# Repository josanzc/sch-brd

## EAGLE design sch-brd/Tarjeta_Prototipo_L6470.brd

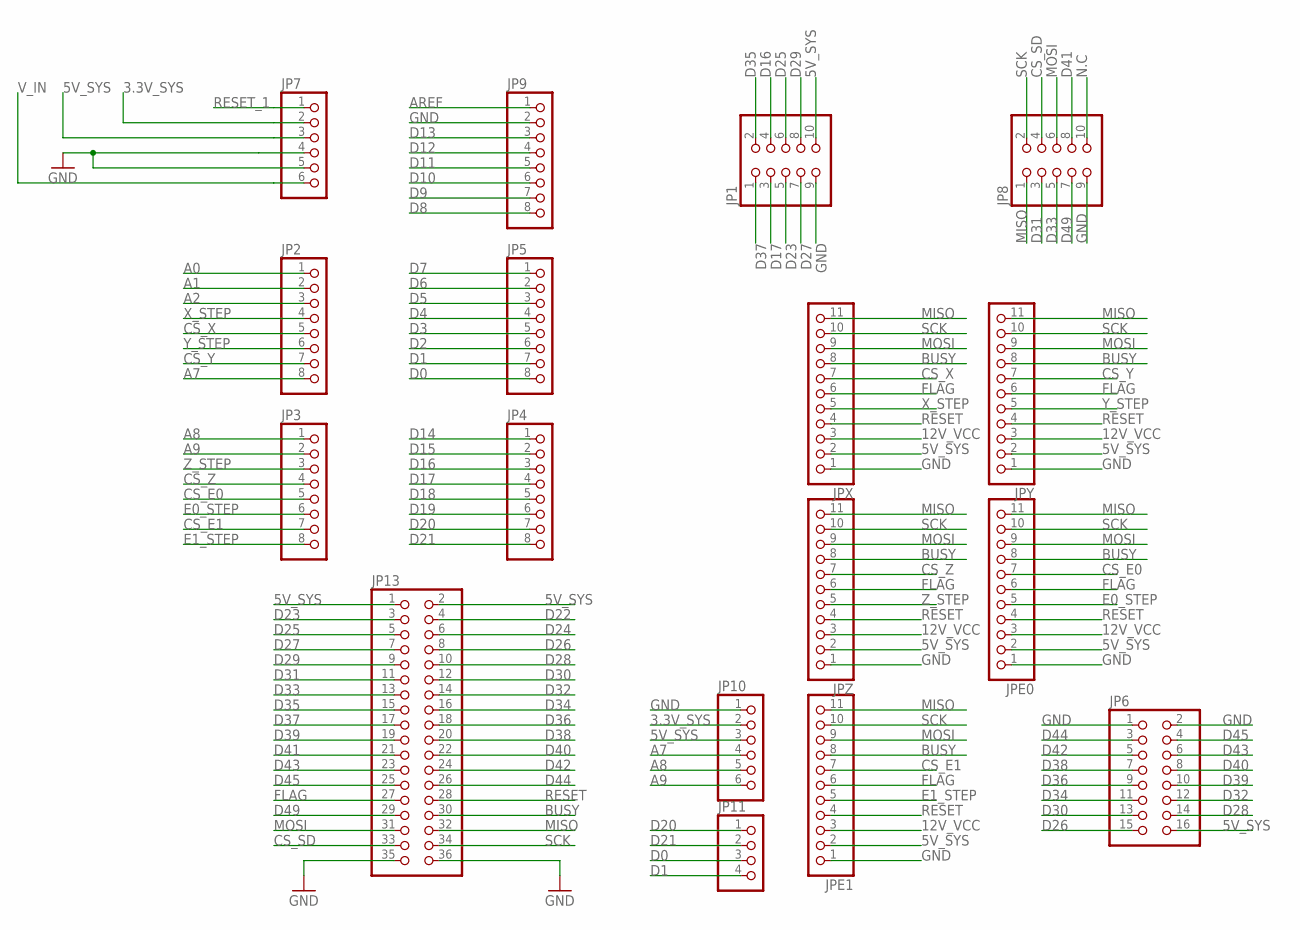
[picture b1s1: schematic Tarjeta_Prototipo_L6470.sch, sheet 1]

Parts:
JP1, JP8: PINHD-2X5; 2X05
JP2, JP3, JP4, JP5, JP9: PINHD-1X8; 1X08
JP6: PINHD-2X8; 2X08
JP7, JP10: PINHD-1X6; 1X06
JP11: PINHD-1X4; 1X04
JP13: PINHD-2X18; 2X18
JPE0, JPE1: PINHD-1X11; 1X11
JPX: PINHD-1X11; 1X11
JPY: PINHD-1X11; 1X11
JPZ: PINHD-1X11; 1X11

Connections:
3.3V_SYS: JP7.2, JP10.2
5V_SYS: JP1.10, JP6.16, JP7.3, JP10.3, JP13.1, JP13.2, JPE0.2, JPE1.2, JPX.2, JPY.2, JPZ.2; also elsewhere on the board
12V_VCC: JPE0.3, JPE1.3, JPX.3, JPY.3, JPZ.3; also elsewhere on the board
A0: JP2.1; also elsewhere on the board
A1: JP2.2; also elsewhere on the board
A2: JP2.3; also elsewhere on the board
A7: JP2.8, JP10.4
A8: JP3.1, JP10.5
A9: JP3.2, JP10.6
AREF: JP9.1
BUSY: JP13.30, JPE0.8, JPE1.8, JPX.8, JPY.8, JPZ.8
CS_E0: JP3.5, JPE0.7
CS_E1: JP3.7, JPE1.7
CS_SD: JP8.4, JP13.33
CS_X: JP2.5, JPX.7
CS_Y: JP2.7, JPY.7
CS_Z: JP3.4, JPZ.7
D0: JP5.8, JP11.3
D1: JP5.7, JP11.4
D2: JP5.6; also elsewhere on the board
D3: JP5.5; also elsewhere on the board
D4: JP5.4; also elsewhere on the board
D5: JP5.3; also elsewhere on the board
D6: JP5.2; also elsewhere on the board
D7: JP5.1; also elsewhere on the board
D8: JP9.8; also elsewhere on the board
D9: JP9.7; also elsewhere on the board
D10: JP9.6; also elsewhere on the board
D11: JP9.5; also elsewhere on the board
D12: JP9.4; also elsewhere on the board
D13: JP9.3; also elsewhere on the board
D14: JP4.1; also elsewhere on the board
D15: JP4.2; also elsewhere on the board
D16: JP1.4, JP4.3
D17: JP1.3, JP4.4
D18: JP4.5; also elsewhere on the board
D19: JP4.6; also elsewhere on the board
D20: JP4.7, JP11.1
D21: JP4.8, JP11.2
D22: JP13.4; also elsewhere on the board
D23: JP1.5, JP13.3
D24: JP13.6; also elsewhere on the board
D25: JP1.6, JP13.5
D26: JP6.15, JP13.8
D27: JP1.7, JP13.7
D28: JP6.14, JP13.10
D29: JP1.8, JP13.9
D30: JP6.13, JP13.12
D31: JP8.3, JP13.11
D32: JP6.12, JP13.14
D33: JP8.5, JP13.13
D34: JP6.11, JP13.16
D35: JP1.2, JP13.15
D36: JP6.9, JP13.18
D37: JP1.1, JP13.17
D38: JP6.7, JP13.20
D39: JP6.10, JP13.19
D40: JP6.8, JP13.22
D41: JP8.8, JP13.21
D42: JP6.5, JP13.24
D43: JP6.6, JP13.23
D44: JP6.3, JP13.26
D45: JP6.4, JP13.25
D49: JP8.7, JP13.29
E0_STEP: JP3.6, JPE0.5
E1_STEP: JP3.8, JPE1.5
FLAG: JP13.27, JPE0.6, JPE1.6, JPX.6, JPY.6, JPZ.6
GND: JP1.9, JP6.1, JP6.2, JP7.4, JP7.5, JP8.9, JP9.2, JP10.1, JP13.35, JP13.36, JPE0.1, JPE1.1, JPX.1, JPY.1, JPZ.1; also elsewhere on the board
MISO: JP8.1, JP13.32, JPE0.11, JPE1.11, JPX.11, JPY.11, JPZ.11
MOSI: JP8.6, JP13.31, JPE0.9, JPE1.9, JPX.9, JPY.9, JPZ.9
N.C: JP8.10
RESET: JP13.28, JPE0.4, JPE1.4, JPX.4, JPY.4, JPZ.4
RESET_1: JP7.1; also elsewhere on the board
SCK: JP8.2, JP13.34, JPE0.10, JPE1.10, JPX.10, JPY.10, JPZ.10
V_IN: JP7.6; also elsewhere on the board
X_STEP: JP2.4, JPX.5
Y_STEP: JP2.6, JPY.5
Z_STEP: JP3.3, JPZ.5

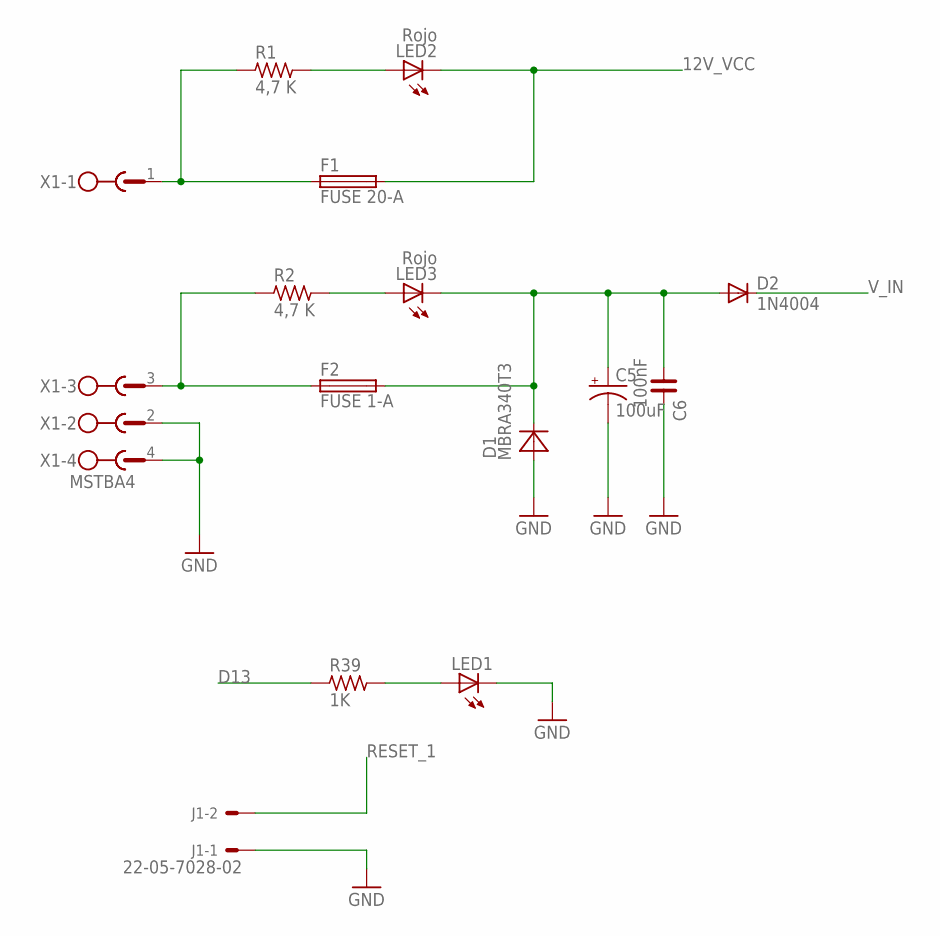
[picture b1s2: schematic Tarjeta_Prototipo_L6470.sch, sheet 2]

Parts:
C5: 100uF; 153CLV-0605
C6: 100nF; C1206
D1: MBRA340T3; SMA
D2: 1N4004; DO41-10
F1: FUSE 20-A; 3557
F2: FUSE 1-A; 3557
J1: 22-05-7028-02; 7395-02
LED1: LEDSMT1206; 1206
LED2, LED3: Rojo; 1206
R1, R2: 4,7 K; R1206
R39: 1K; R1206
X1: MSTBA4

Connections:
12V_IN1: F1.P$1 (1), F1.P$2 (1), R1.1, X1.1
12V_IN2: F2.P$1 (1), F2.P$2 (1), R2.1, X1.3
12V_VCC: F1.P$3 (2), F1.P$4 (2), LED2.C; also elsewhere on the board
D13: R39.1; also elsewhere on the board
GND: C5.-, C6.2, D1.A, J1.1, LED1.C, X1.2, X1.4; also elsewhere on the board
unnamed: LED1.A, R39.2
unnamed: LED2.A, R1.2
unnamed: LED3.A, R2.2
unnamed: C5.+, C6.1, D1.C, D2.A, F2.P$3 (2), F2.P$4 (2), LED3.C
RESET_1: J1.2; also elsewhere on the board
V_IN: D2.C; also elsewhere on the board

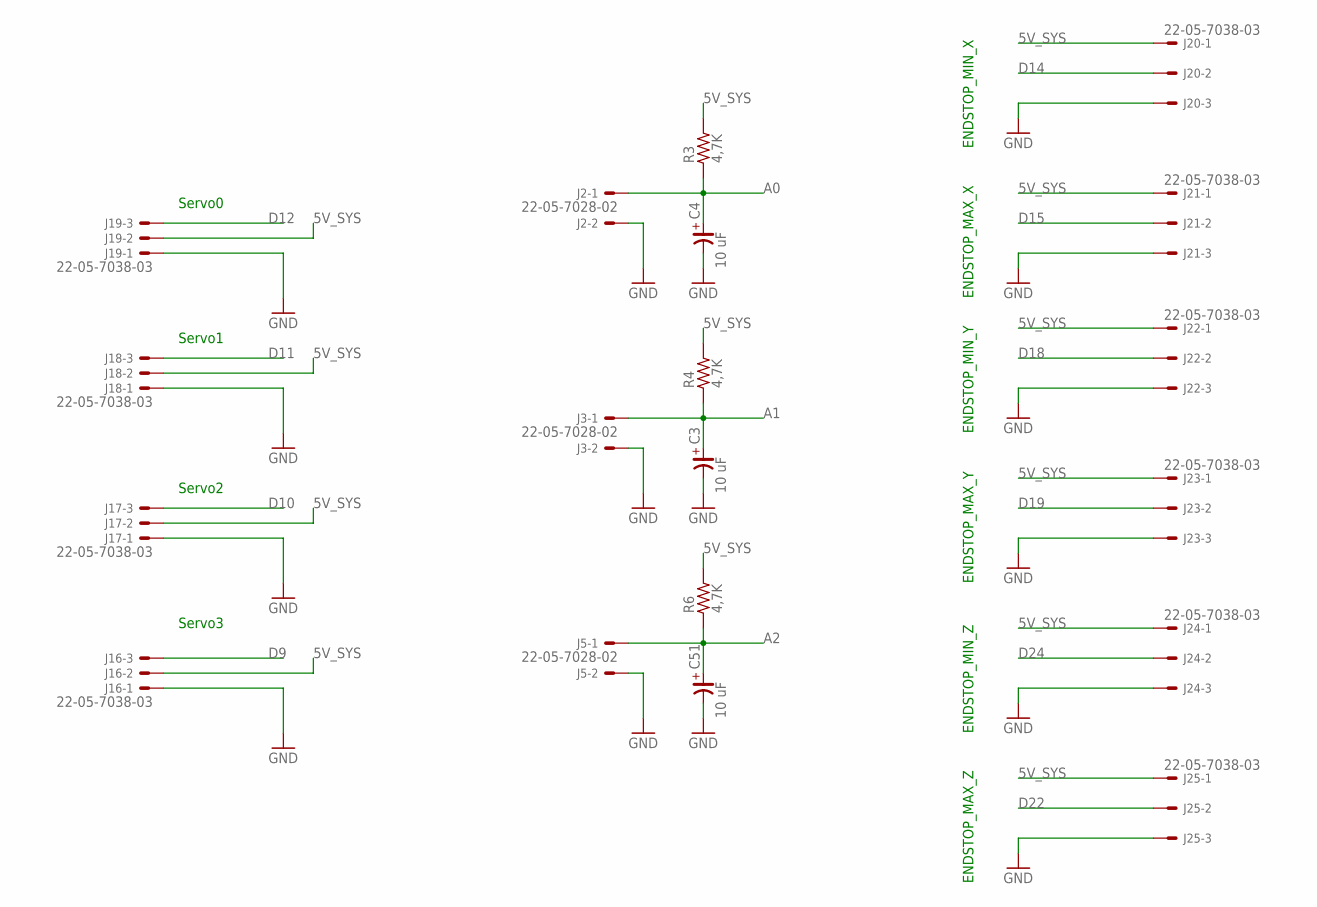
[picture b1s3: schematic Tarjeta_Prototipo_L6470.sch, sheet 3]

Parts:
C3, C4, C51: 10 uF; CSV-B
J2, J3, J5: 22-05-7028-02; 7395-02
J16, J17, J18, J19, J20, J21, J22, J23, J24, J25: 22-05-7038-03; 7395-03
R3, R4, R6: 4,7K; R1206

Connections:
5V_SYS: J16.2, J17.2, J18.2, J19.2, J20.1, J21.1, J22.1, J23.1, J24.1, J25.1, R3.2, R4.2, R6.2; also elsewhere on the board
A0: C4.+, J2.1, R3.1; also elsewhere on the board
A1: C3.+, J3.1, R4.1; also elsewhere on the board
A2: C51.+, J5.1, R6.1; also elsewhere on the board
D9: J16.3; also elsewhere on the board
D10: J17.3; also elsewhere on the board
D11: J18.3; also elsewhere on the board
D12: J19.3; also elsewhere on the board
D14: J20.2; also elsewhere on the board
D15: J21.2; also elsewhere on the board
D18: J22.2; also elsewhere on the board
D19: J23.2; also elsewhere on the board
D22: J25.2; also elsewhere on the board
D24: J24.2; also elsewhere on the board
GND: C3.-, C4.-, C51.-, J2.2, J3.2, J5.2, J16.1, J17.1, J18.1, J19.1, J20.3, J21.3, J22.3, J23.3, J24.3, J25.3; also elsewhere on the board

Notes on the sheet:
Servo3
Servo2
Servo1
Servo0
ENDSTOP_MIN_X
ENDSTOP_MAX_X
ENDSTOP_MIN_Y
ENDSTOP_MAX_Y
ENDSTOP_MAX_Z
ENDSTOP_MIN_Z

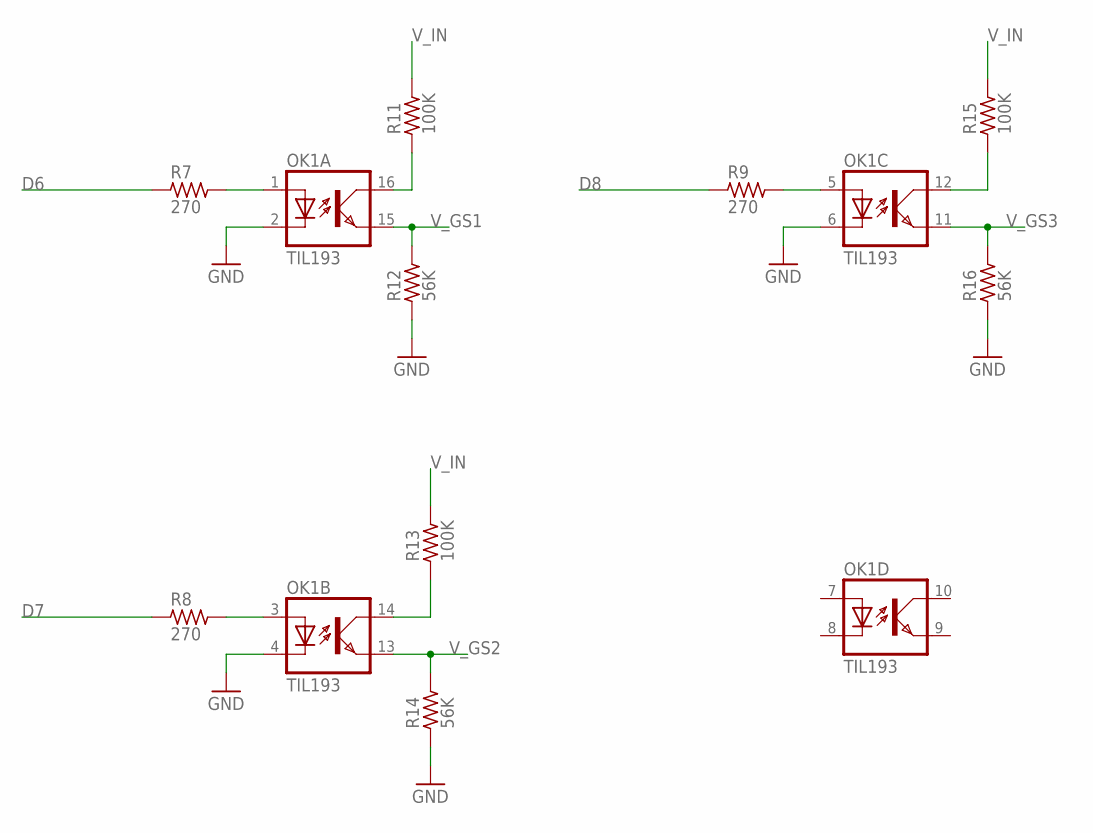
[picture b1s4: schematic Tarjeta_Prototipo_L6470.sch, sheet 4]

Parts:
OK1: TIL193; DIL16
R7, R8, R9: 270; R1206
R11, R13, R15: 100K; R1206
R12, R14, R16: 56K; R1206

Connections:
D6: R7.1; also elsewhere on the board
D7: R8.1; also elsewhere on the board
D8: R9.1; also elsewhere on the board
GND: OK1.2 (C), OK1.4 (C), OK1.6 (C), R12.1, R14.1, R16.1; also elsewhere on the board
unnamed: OK1.1 (A), R7.2
unnamed: OK1.3 (A), R8.2
unnamed: OK1.5 (A), R9.2
unnamed: OK1.16 (COL), R11.1
unnamed: OK1.14 (COL), R13.1
unnamed: OK1.12 (COL), R15.1
V_GS1: OK1.15 (EMIT), R12.2; also elsewhere on the board
V_GS2: OK1.13 (EMIT), R14.2; also elsewhere on the board
V_GS3: OK1.11 (EMIT), R16.2; also elsewhere on the board
V_IN: R11.2, R13.2, R15.2; also elsewhere on the board

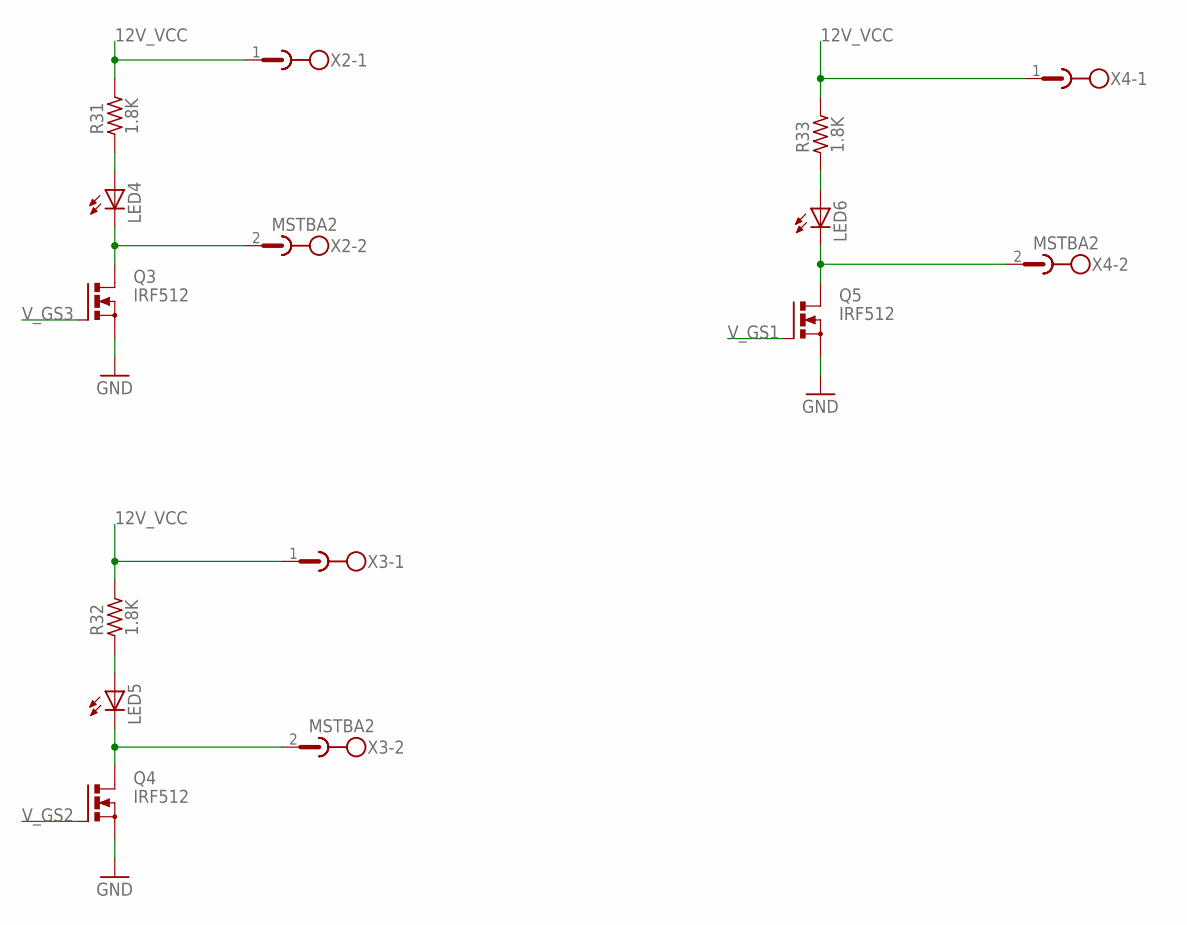
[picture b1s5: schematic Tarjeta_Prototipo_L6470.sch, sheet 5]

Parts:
LED4, LED5, LED6: LEDSMT1206; 1206
Q3, Q4, Q5: IRF512; TO220BV
R31, R32, R33: 1.8K; R1206
X2, X3, X4: MSTBA2

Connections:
12V_VCC: R31.2, R32.2, R33.2, X2.1, X3.1, X4.1; also elsewhere on the board
GND: Q3.S, Q4.S, Q5.S; also elsewhere on the board
unnamed: LED6.C, Q5.D, X4.2
unnamed: LED4.A, R31.1
unnamed: LED5.C, Q4.D, X3.2
unnamed: LED5.A, R32.1
unnamed: LED6.A, R33.1
unnamed: LED4.C, Q3.D, X2.2
V_GS1: Q5.G; also elsewhere on the board
V_GS2: Q4.G; also elsewhere on the board
V_GS3: Q3.G; also elsewhere on the board

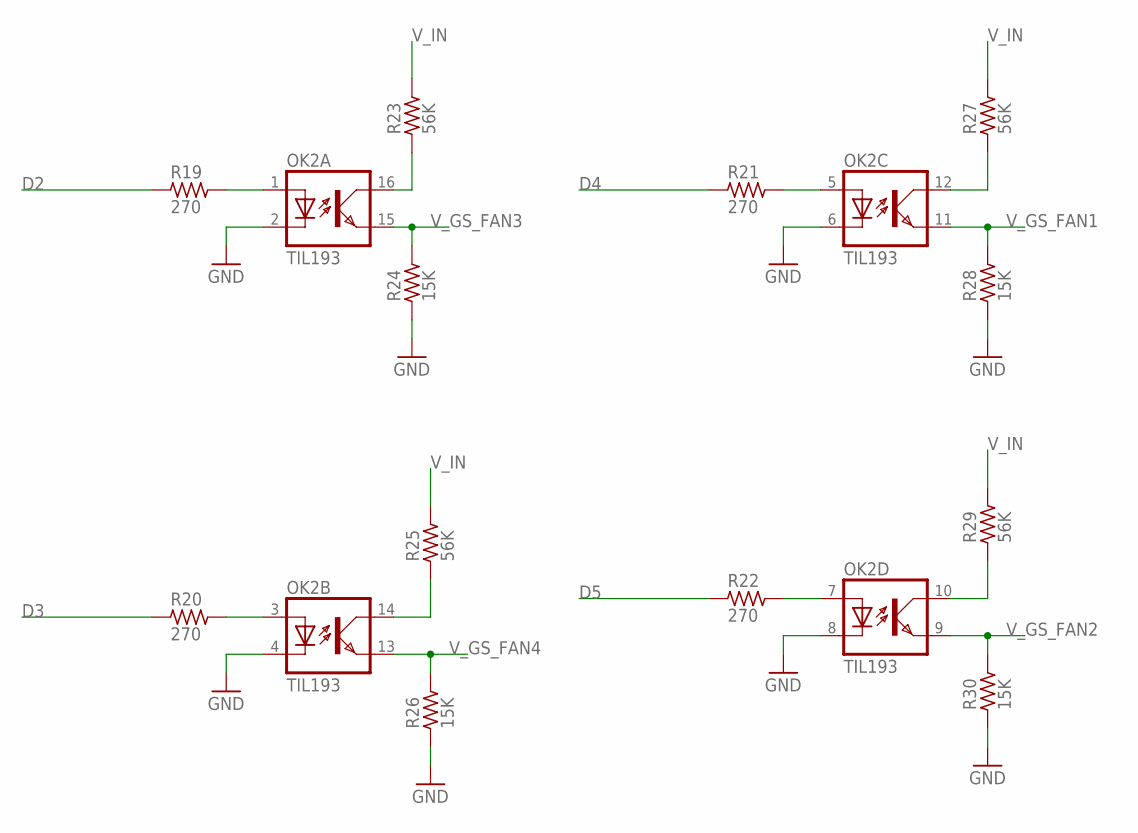
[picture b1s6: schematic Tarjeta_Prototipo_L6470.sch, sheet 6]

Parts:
OK2: TIL193; DIL16
R19, R20, R21, R22: 270; R1206
R23, R25, R27, R29: 56K; R1206
R24, R26, R28, R30: 15K; R1206

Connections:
D2: R19.1; also elsewhere on the board
D3: R20.1; also elsewhere on the board
D4: R21.1; also elsewhere on the board
D5: R22.1; also elsewhere on the board
GND: OK2.2 (C), OK2.4 (C), OK2.6 (C), OK2.8 (C), R24.1, R26.1, R28.1, R30.1; also elsewhere on the board
unnamed: OK2.1 (A), R19.2
unnamed: OK2.3 (A), R20.2
unnamed: OK2.5 (A), R21.2
unnamed: OK2.7 (A), R22.2
unnamed: OK2.16 (COL), R23.1
unnamed: OK2.14 (COL), R25.1
unnamed: OK2.12 (COL), R27.1
unnamed: OK2.10 (COL), R29.1
V_GS_FAN1: OK2.11 (EMIT), R28.2; also elsewhere on the board
V_GS_FAN2: OK2.9 (EMIT), R30.2; also elsewhere on the board
V_GS_FAN3: OK2.15 (EMIT), R24.2; also elsewhere on the board
V_GS_FAN4: OK2.13 (EMIT), R26.2; also elsewhere on the board
V_IN: R23.2, R25.2, R27.2, R29.2; also elsewhere on the board

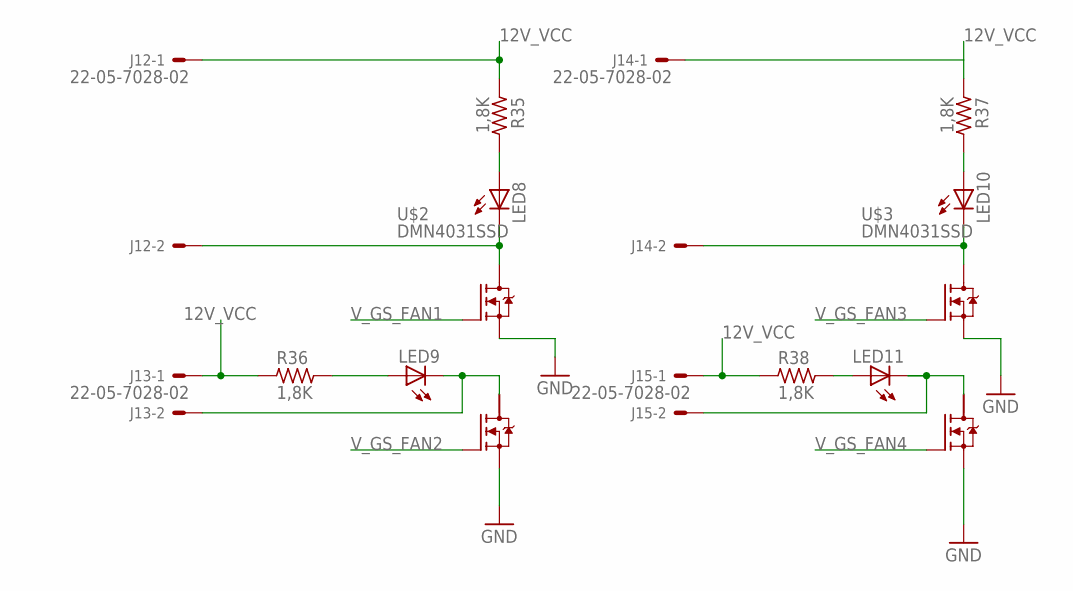
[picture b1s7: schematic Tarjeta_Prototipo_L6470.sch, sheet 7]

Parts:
J12, J13, J14, J15: 22-05-7028-02; 7395-02
LED8, LED9, LED10, LED11: LEDSMT1206; 1206
R35, R36, R37, R38: 1,8K; R1206
U$2, U$3: DMN4031SSD

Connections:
12V_VCC: J12.1, J13.1, J14.1, J15.1, R35.1, R36.1, R37.1, R38.1; also elsewhere on the board
GND: U$2.1 (S2), U$2.3 (S1), U$3.1 (S2), U$3.3 (S1); also elsewhere on the board
unnamed: LED11.A, R38.2
unnamed: J15.2, LED11.C, U$3.7 (D2), U$3.8 (D2)
unnamed: LED9.A, R36.2
unnamed: J13.2, LED9.C, U$2.7 (D2), U$2.8 (D2)
unnamed: LED8.A, R35.2
unnamed: J14.2, LED10.C, U$3.5 (D1), U$3.6 (D1)
unnamed: J12.2, LED8.C, U$2.5 (D1), U$2.6 (D1)
unnamed: LED10.A, R37.2
V_GS_FAN1: U$2.4 (G1); also elsewhere on the board
V_GS_FAN2: U$2.2 (G2); also elsewhere on the board
V_GS_FAN3: U$3.4 (G1); also elsewhere on the board
V_GS_FAN4: U$3.2 (G2); also elsewhere on the board

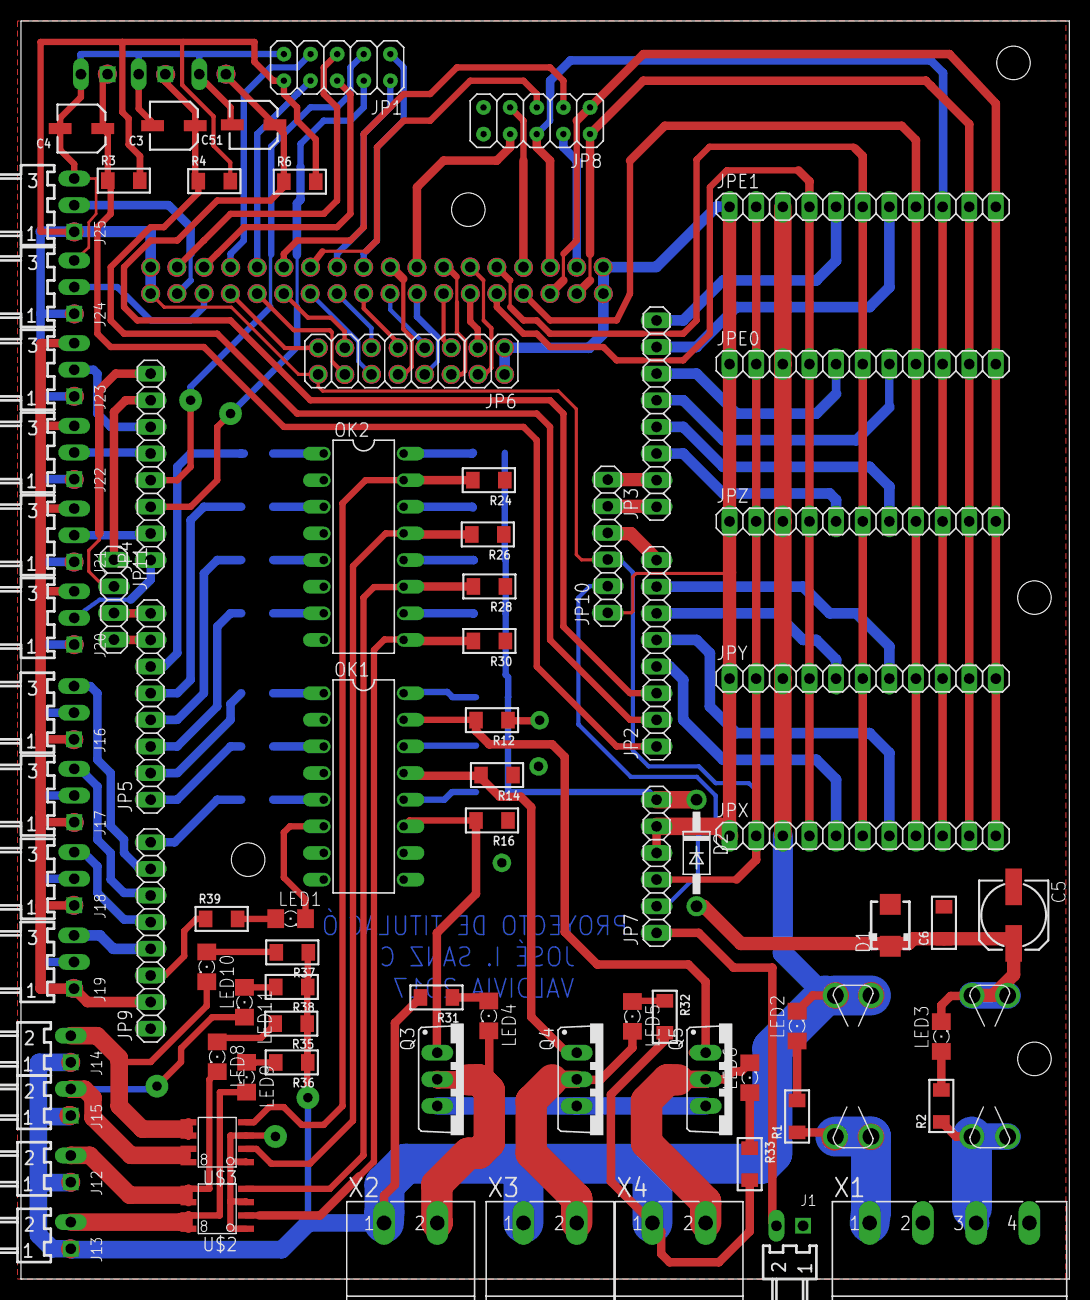
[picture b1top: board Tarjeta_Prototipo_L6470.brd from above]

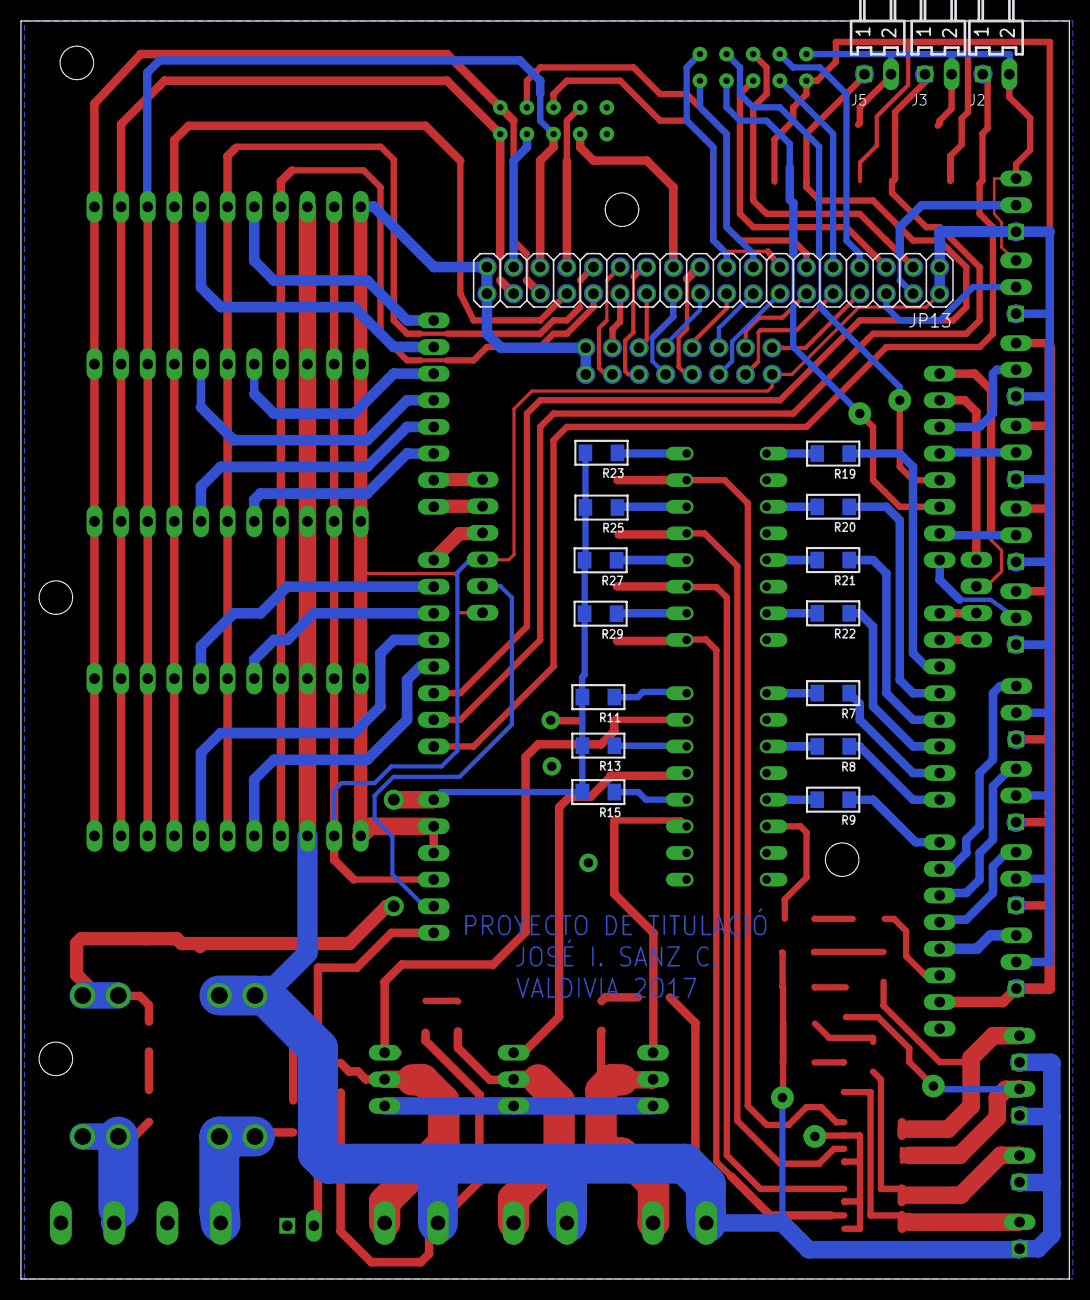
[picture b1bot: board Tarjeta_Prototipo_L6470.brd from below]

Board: 2 copper layers, 100.0 x 120.0 mm, 99 parts (18 on the bottom side), 117 nets.

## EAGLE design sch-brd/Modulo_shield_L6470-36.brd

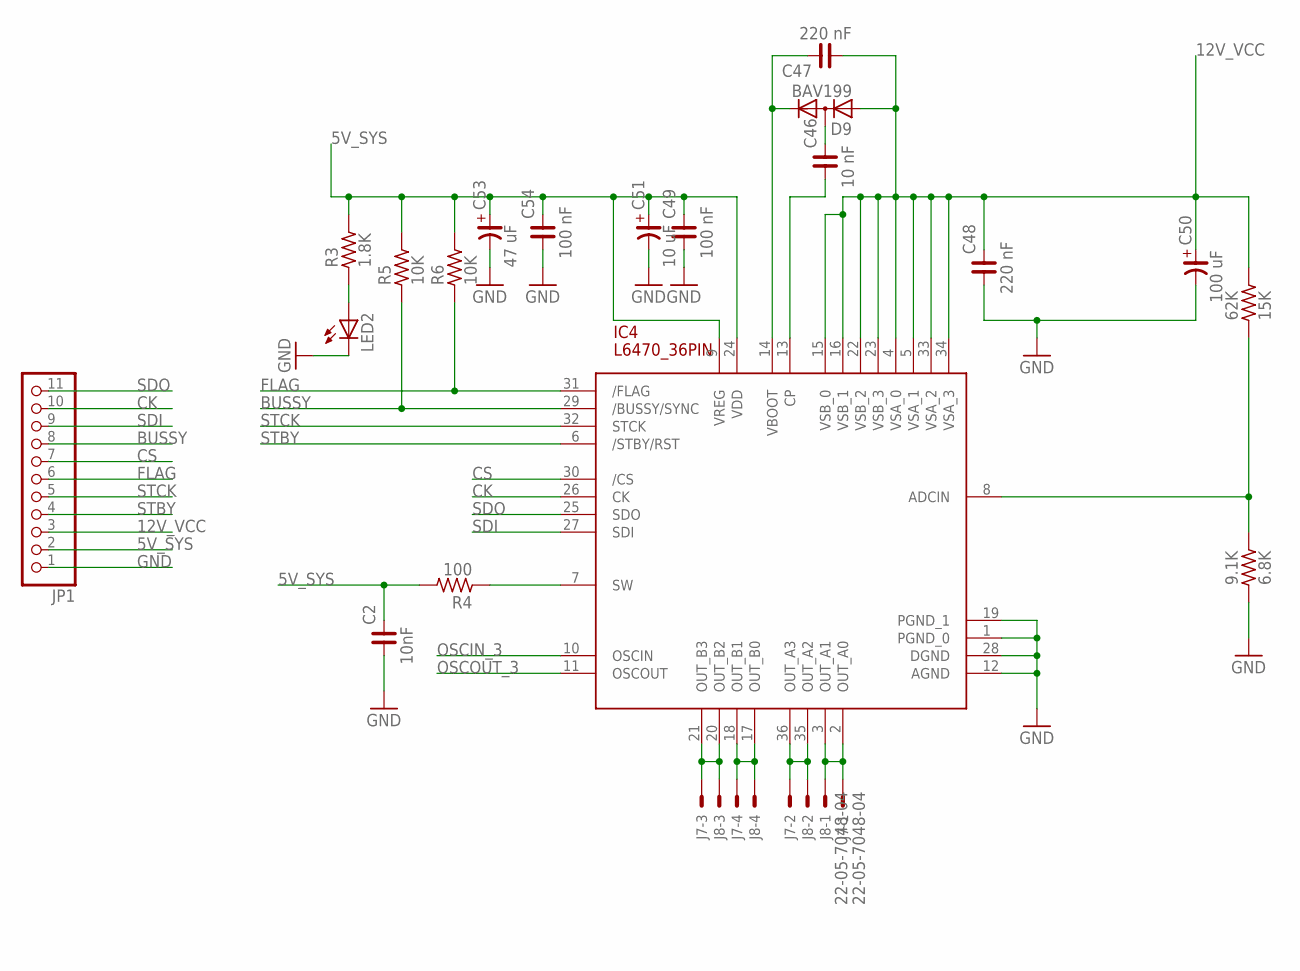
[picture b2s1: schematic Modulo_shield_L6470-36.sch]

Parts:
9.1K: 6.8K; R1206
62K: 15K; R1206
C2: 10nF; C1206
C46: 10 nF; C1206
C47, C48: 220 nF; C1206
C49, C54: 100 nF; C1206
C50: 100 uF; CSV-D
C51: 10 uF; CSV-B
C53: 47 uF; CSV-B
D9: BAV199; SOT23
IC4: L6470_36PIN
J7, J8: 22-05-7048-04; 7395-04
JP1: PINHD-1X11/90; 1X11/90
LED2: LEDCHIPLED_1206; CHIPLED_1206
R3: 1.8K; R1206
R4: 100; R1206
R5, R6: 10K; R1206

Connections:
5V_SYS: C2.2, C49.2, C51.+, C53.+, C54.2, IC4.9 (VREG), IC4.24 (VDD), JP1.2, R3.2, R4.2, R5.2, R6.2
12V_VCC: 62K.2, C47.1, C48.2, C50.+, D9.1 (A), IC4.4 (VSA_0), IC4.5 (VSA_1), IC4.15 (VSB_0), IC4.16 (VSB_1), IC4.22 (VSB_2), IC4.23 (VSB_3), IC4.33 (VSA_2), IC4.34 (VSA_3), JP1.3
BUSSY: IC4.29 (/BUSSY/SYNC), JP1.8, R5.1
CK: IC4.26 (CK), JP1.10
CS: IC4.30 (/CS), JP1.7
FLAG: IC4.31 (/FLAG), JP1.6, R6.1
GND: 9.1K.1, C2.1, C48.1, C49.1, C50.-, C51.-, C53.-, C54.1, IC4.1 (PGND_0), IC4.12 (AGND), IC4.19 (PGND_1), IC4.28 (DGND), JP1.1, LED2.C
unnamed: IC4.2 (OUT_A0), IC4.3 (OUT_A1), J7.1, J8.1
unnamed: IC4.20 (OUT_B2), IC4.21 (OUT_B3), J7.3, J8.3
unnamed: LED2.A, R3.1
unnamed: IC4.7 (SW), R4.1
unnamed: IC4.35 (OUT_A2), IC4.36 (OUT_A3), J7.2, J8.2
unnamed: IC4.17 (OUT_B0), IC4.18 (OUT_B1), J7.4, J8.4
unnamed: C46.2, D9.3 (AC)
unnamed: C46.1, IC4.13 (CP)
unnamed: C47.2, D9.2 (C), IC4.14 (VBOOT)
unnamed: 9.1K.2, 62K.1, IC4.8 (ADCIN)
OSCIN_3: IC4.10 (OSCIN)
OSCOUT_3: IC4.11 (OSCOUT)
SDI: IC4.27 (SDI), JP1.9
SDO: IC4.25 (SDO), JP1.11
STBY: IC4.6 (/STBY/RST), JP1.4
STCK: IC4.32 (STCK), JP1.5

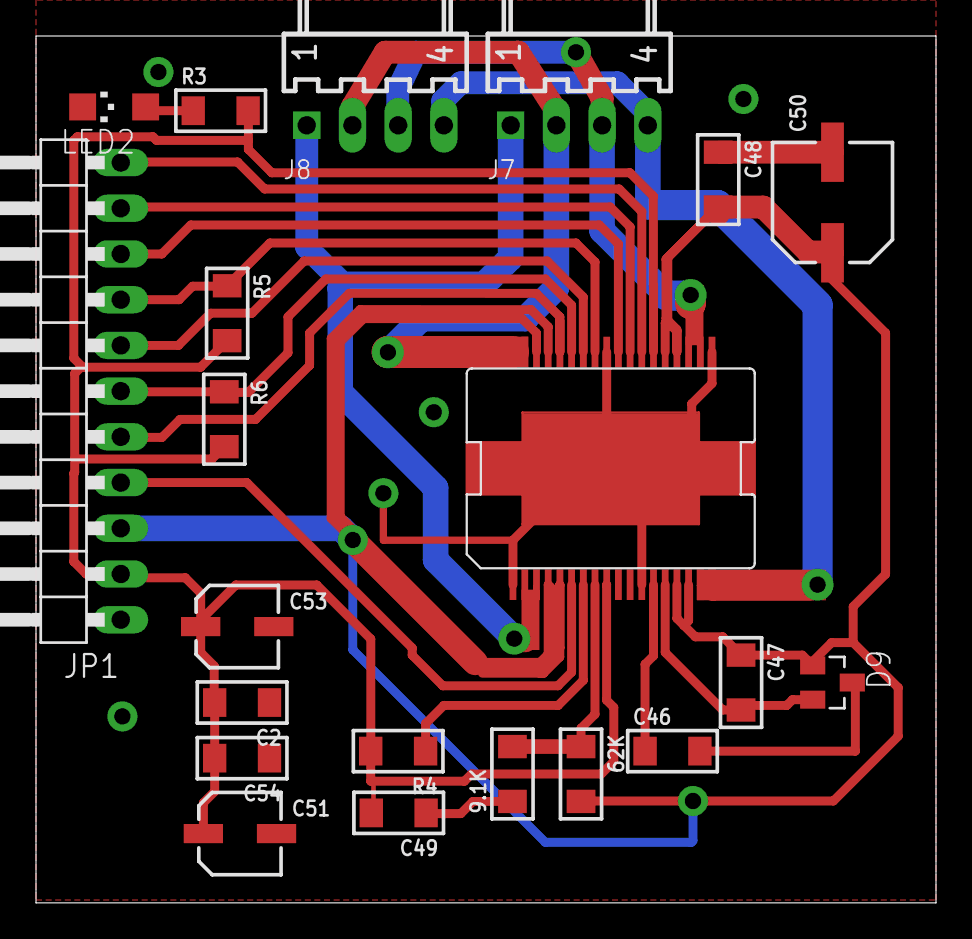
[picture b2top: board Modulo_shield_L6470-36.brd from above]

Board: 2 copper layers, 50.0 x 48.2 mm, 21 parts (0 on the bottom side), 21 nets.

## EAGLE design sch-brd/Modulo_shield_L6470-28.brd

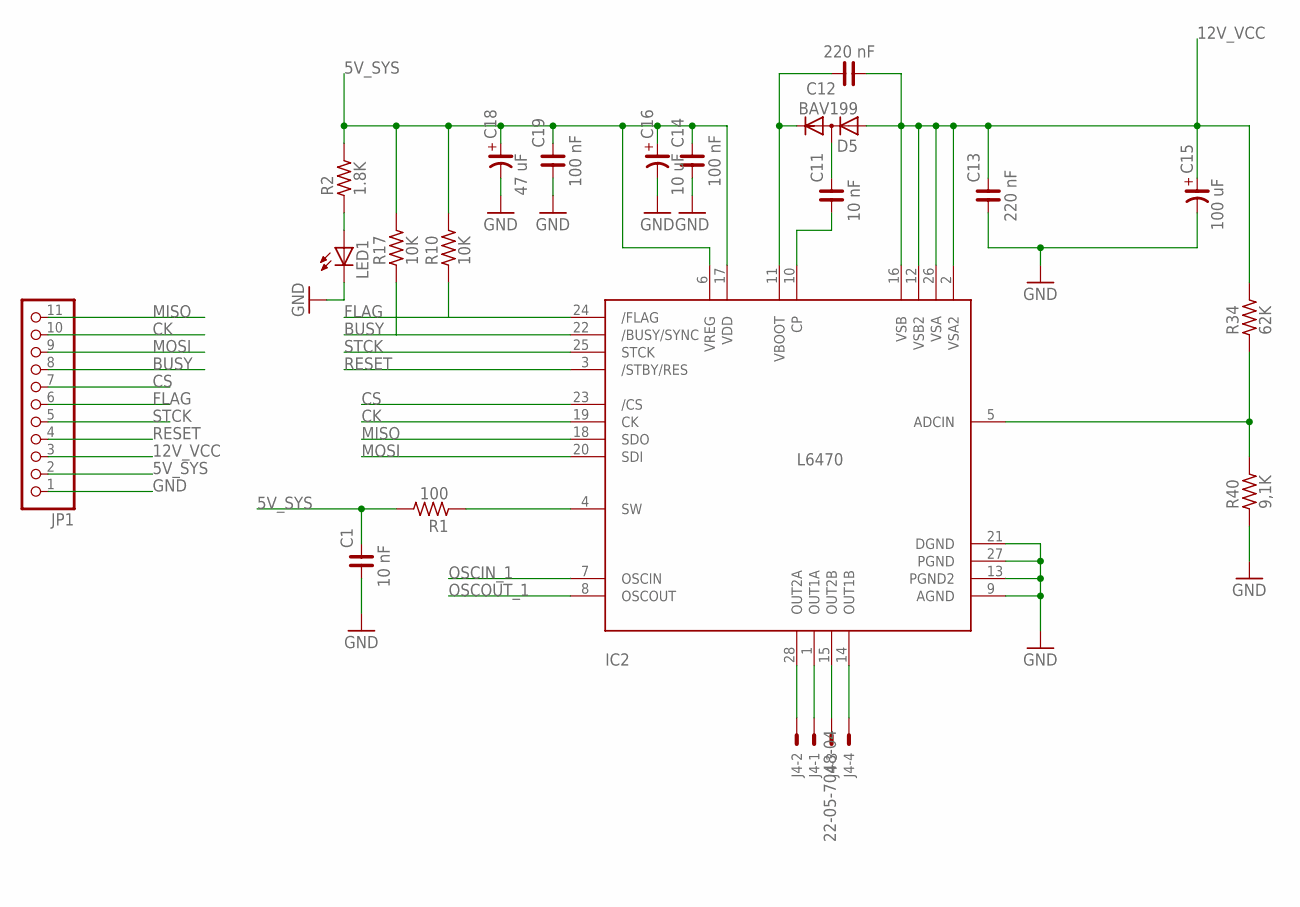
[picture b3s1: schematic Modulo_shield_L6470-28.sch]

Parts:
C1, C11: 10 nF; C1206
C12, C13: 220 nF; C1206
C14, C19: 100 nF; C1206
C15: 100 uF; CSV-D
C16: 10 uF; CSV-B
C18: 47 uF; CSV-B
D5: BAV199; SOT23
IC2: L6470; HTSSOP28
J4: 22-05-7048-04; 7395-04
JP1: PINHD-1X11/90; 1X11/90
LED1: LEDCHIPLED_1206; CHIPLED_1206
R1: 100; R1206
R2: 1.8K; R1206
R10, R17: 10K; R1206
R34: 62K; R1206
R40: 9,1K; R1206

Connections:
5V_SYS: C1.2, C14.2, C16.+, C18.+, C19.2, IC2.6 (VREG), IC2.17 (VDD), JP1.2, R1.2, R2.2, R10.2, R17.2
12V_VCC: C12.1, C13.2, C15.+, D5.1 (A), IC2.2 (VSA2), IC2.12 (VSB2), IC2.16 (VSB), IC2.26 (VSA), JP1.3, R34.2
A1: IC2.1 (OUT1A), J4.1
A2: IC2.28 (OUT2A), J4.2
BUSY: IC2.22 (/BUSY/SYNC), JP1.8, R17.1
CK: IC2.19 (CK), JP1.10
CS: IC2.23 (/CS), JP1.7
FLAG: IC2.24 (/FLAG), JP1.6, R10.1
GND: C1.1, C13.1, C14.1, C15.-, C16.-, C18.-, C19.1, IC2.9 (AGND), IC2.13 (PGND2), IC2.21 (DGND), IC2.27 (PGND), JP1.1, LED1.C, R40.1
MISO: IC2.18 (SDO), JP1.11
MOSI: IC2.20 (SDI), JP1.9
unnamed: IC2.4 (SW), R1.1
unnamed: IC2.15 (OUT2B), J4.3
unnamed: IC2.14 (OUT1B), J4.4
unnamed: C11.2, D5.3 (AC)
unnamed: C11.1, IC2.10 (CP)
unnamed: LED1.A, R2.1
unnamed: IC2.5 (ADCIN), R34.1, R40.2
OSCIN_1: IC2.7 (OSCIN)
OSCOUT_1: IC2.8 (OSCOUT)
RESET: IC2.3 (/STBY/RES), JP1.4
STCK: IC2.25 (STCK), JP1.5
VBOOT_1: C12.2, D5.2 (C), IC2.11 (VBOOT)

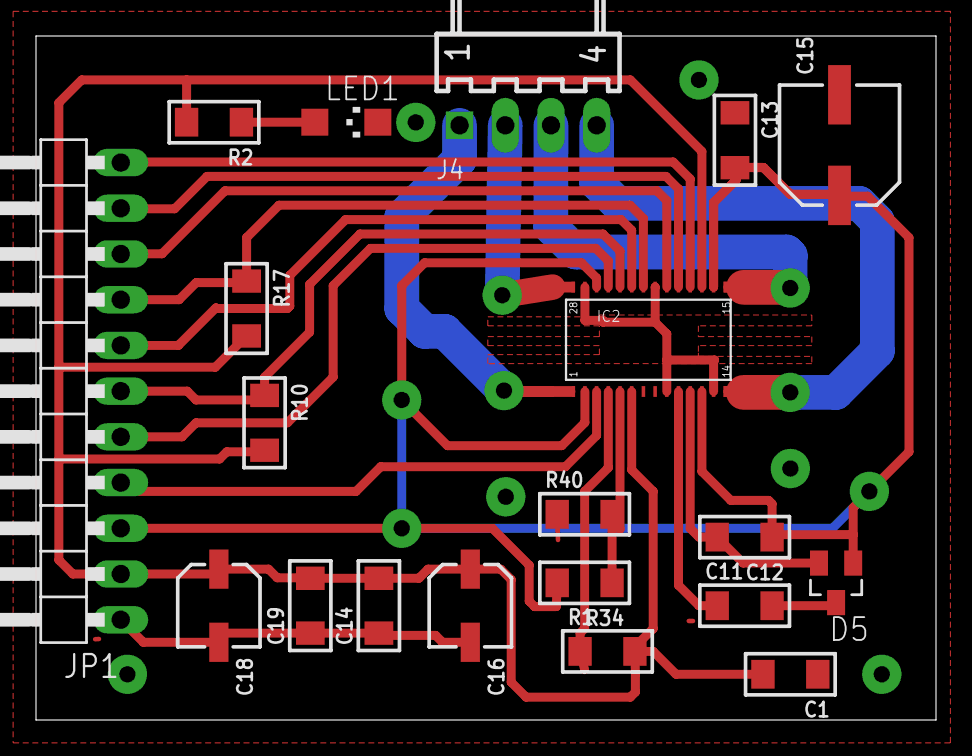
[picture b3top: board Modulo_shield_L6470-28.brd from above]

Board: 2 copper layers, 50.0 x 38.0 mm, 20 parts (0 on the bottom side), 21 nets.

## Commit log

2017-09-16 Esquemas
    sch-brd
2017-09-18 Archivos_para_planchado_de_PCB
    Archivos_para_planchado_de_PCB
2017-09-19 Marlin 1.1.X
    Marlin 1.1.X

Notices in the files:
parts and their libraries:
tesis-master-smd: Copyright (C) 2007, Bob Starr
